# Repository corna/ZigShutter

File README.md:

# ZigShutter

ZigShutter is a platform for the control of window shutters and IAS.

It features:
 * ZigBee connectivity through a nRF52840 module
 * AC power supply
 * Control of two outputs with SSR, to control the two directions of a window shutter motor
 * Two inputs for window opening sensors
 * Eight GPIOs

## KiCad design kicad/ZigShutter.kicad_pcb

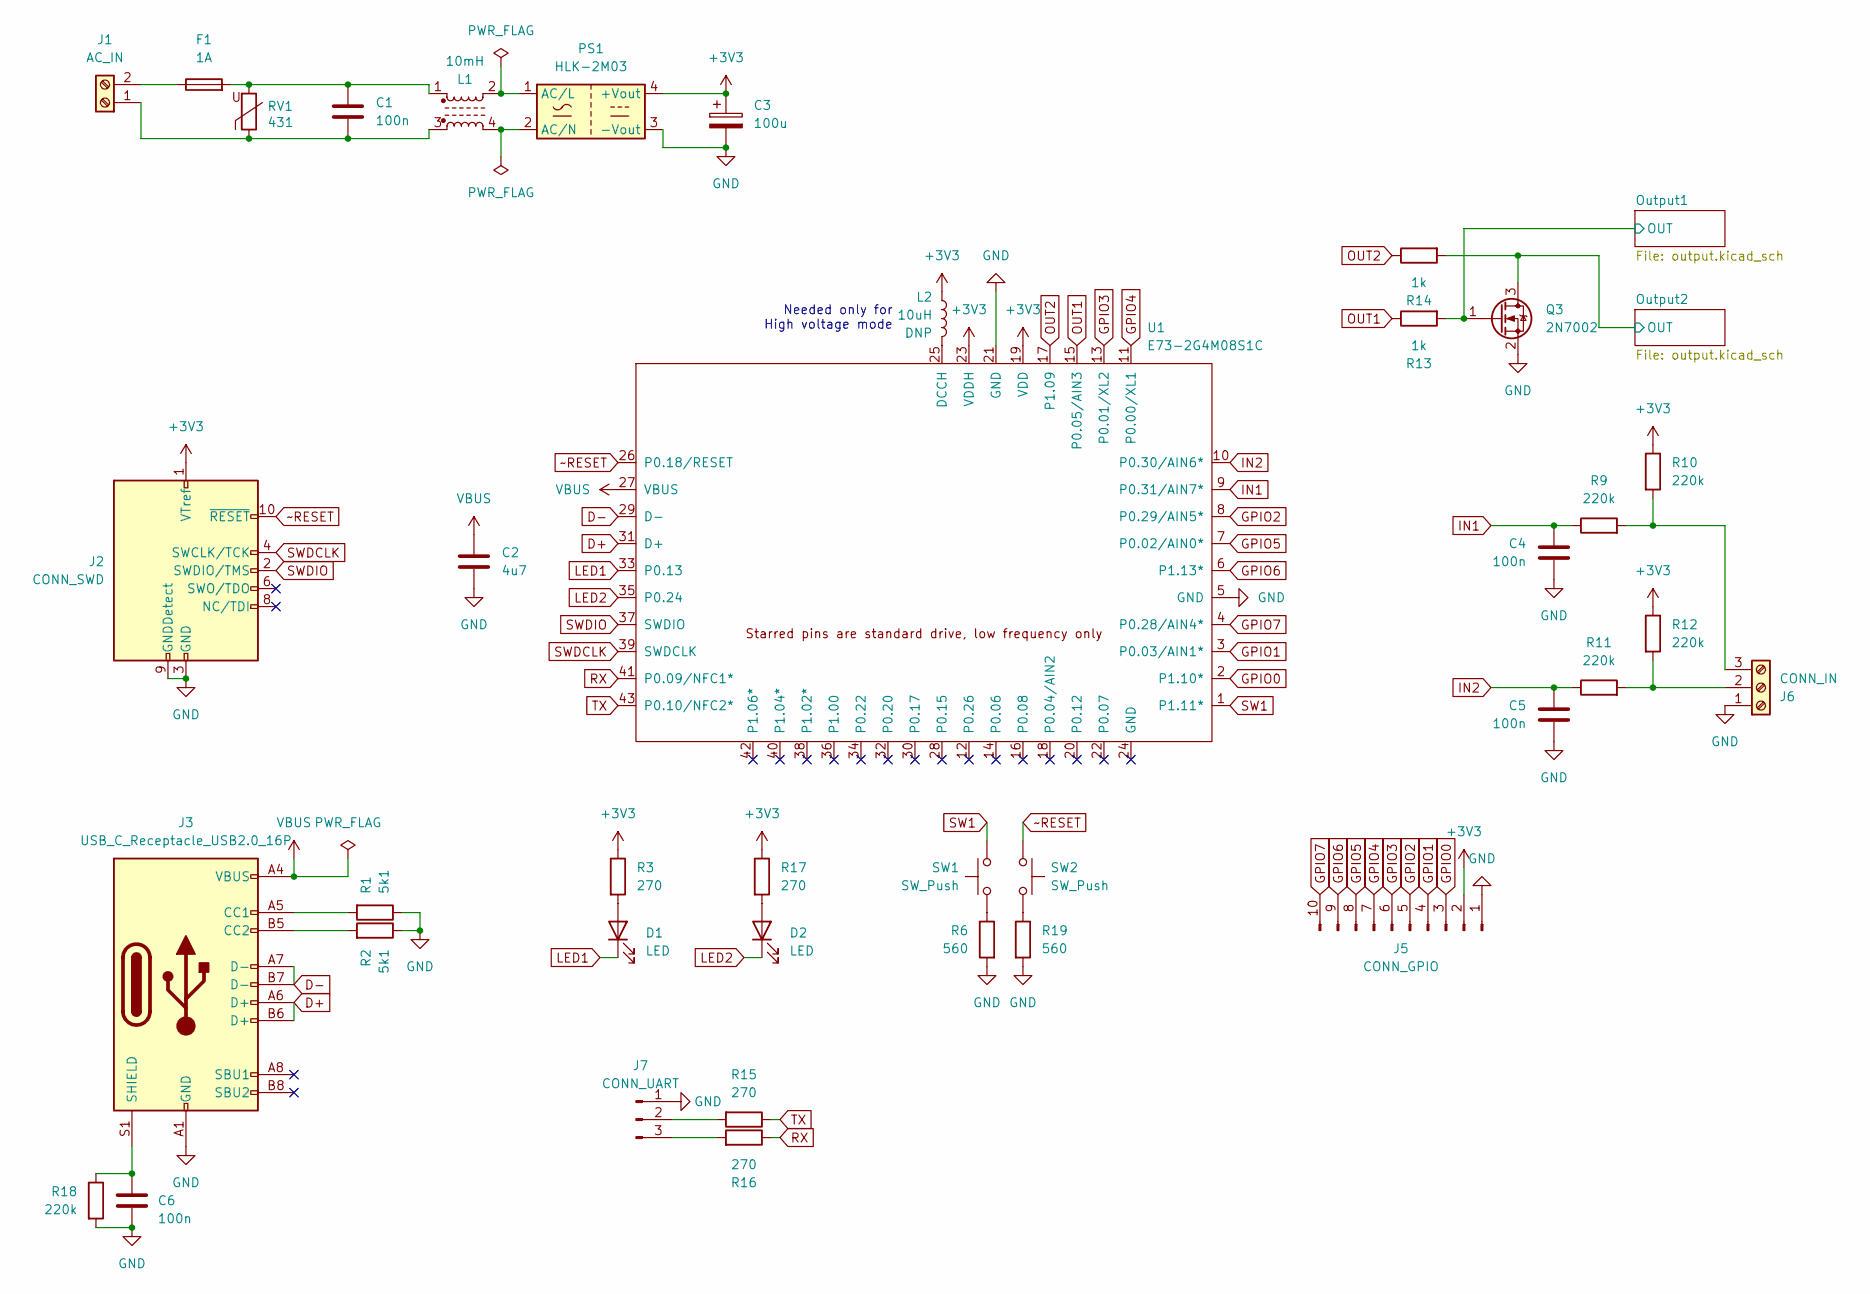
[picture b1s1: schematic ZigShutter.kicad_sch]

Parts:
C1: 100n; C_Rect_L11.5mm_W5.0mm_P10.00mm_MKT
C2: 4u7; C_0603_1608Metric
C3: 100u; CP_EIA-3528-21_Kemet-B
C4, C5, C6: 100n; C_0603_1608Metric
D1, D2: LED; LED_0603_1608Metric
F1: 1A; XFCN_PTF-77
J1: AC_IN; TerminalBlock_Phoenix_MKDS-1,5-2_1x02_P5.00mm_Horizontal
J2: CONN_SWD; PinHeader_2x05_P1.27mm_Vertical_SMD
J3: USB_C_Receptacle_USB2.0_16P; USB_C_Receptacle_XKB_U262_161N_4BSS73_T
J5: CONN_GPIO; PinHeader_1x10_P2.54mm_Vertical
J6: CONN_IN; TerminalBlock_Phoenix_MPT-0,5-3-2.54_1x03_P2.54mm_Horizontal
J7: CONN_UART; PinHeader_1x03_P2.54mm_Vertical
L1: 10mH; UU9.8
L2: 10uH; L_0805_2012Metric
PS1: HLK-2M03; Converter_ACDC_Hi-Link_HLK-2Mxx
Q3: 2N7002; SOT-23
R1, R2: 5k1; R_0603_1608Metric
R3, R15, R16, R17: 270; R_0603_1608Metric
R6, R19: 560; R_0603_1608Metric
R9, R10, R11, R12, R18: 220k; R_0603_1608Metric
R13, R14: 1k; R_0603_1608Metric
RV1: 431; RV_3225
SW1, SW2: SW_Push; SW_Push_SPST_NO_Alps_SKRK
U1: E73-2G4M08S1C

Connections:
+3V3: C3.1, J2.1 (VTref), J5.2, L2.1, PS1.4 (+Vout), R3.1, R10.1, R12.1, R17.1, U1.19 (VDD), U1.23 (VDDH); also elsewhere on the board
/Output1/OUT: Q3.1 (G), R13.2; also elsewhere on the board
/Output2/OUT: Q3.3 (D), R14.2; also elsewhere on the board
D+: J3.A6 (D+), J3.B6 (D+), U1.31 (D+)
D-: J3.A7 (D-), J3.B7 (D-), U1.29 (D-)
GND: C2.2, C3.2, C4.2, C5.2, C6.2, J2.3 (GND), J2.5 (GND), J2.9 (GNDDetect), J3.A1 (GND), J3.A12 (GND), J3.B1 (GND), J3.B12 (GND), J5.1, J6.1, J7.1, PS1.3 (-Vout), Q3.2 (S), R1.1, R2.1, R6.2, R18.2, R19.2, U1.5 (GND), U1.21 (GND); also elsewhere on the board
GPIO0: J5.3, U1.2 (P1.10*)
GPIO1: J5.4, U1.3 (P0.03/AIN1*)
GPIO2: J5.5, U1.8 (P0.29/AIN5*)
GPIO3: J5.6, U1.13 (P0.01/XL2)
GPIO4: J5.7, U1.11 (P0.00/XL1)
GPIO5: J5.8, U1.7 (P0.02/AIN0*)
GPIO6: J5.9, U1.6 (P1.13*)
GPIO7: J5.10, U1.4 (P0.28/AIN4*)
IN1: C4.1, R9.1, U1.9 (P0.31/AIN7*)
IN2: C5.1, R11.1, U1.10 (P0.30/AIN6*)
LED1: D1.1 (K), U1.33 (P0.13)
LED2: D2.1 (K), U1.35 (P0.24)
unnamed: C1.1, F1.2, L1.1, RV1.2
unnamed: D1.2 (A), R3.2
unnamed: D2.2 (A), R17.2
unnamed: C1.2, J1.1, L1.3, RV1.1
unnamed: F1.1, J1.2
unnamed: J3.A5 (CC1), R1.2
unnamed: J3.B5 (CC2), R2.2
unnamed: C6.1, J3.S1 (SHIELD), R18.1
unnamed: J6.2, R11.2, R12.2
unnamed: J6.3, R9.2, R10.2
unnamed: J7.2, R15.2
unnamed: J7.3, R16.2
unnamed: L1.2, PS1.1 (AC/L)
unnamed: L1.4, PS1.2 (AC/N)
unnamed: R6.1, SW1.2
unnamed: R19.1, SW2.2
unnamed: L2.2, U1.25 (DCCH)
OUT1: R13.1, U1.15 (P0.05/AIN3)
OUT2: R14.1, U1.17 (P1.09)
RX: R16.1, U1.41 (P0.09/NFC1*)
SW1: SW1.1, U1.1 (P1.11*)
SWDCLK: J2.4 (SWCLK/TCK), U1.39 (SWDCLK)
SWDIO: J2.2 (SWDIO/TMS), U1.37 (SWDIO)
TX: R15.1, U1.43 (P0.10/NFC2*)
VBUS: C2.1, J3.A4 (VBUS), J3.A9 (VBUS), J3.B4 (VBUS), J3.B9 (VBUS), U1.27 (VBUS)
~RESET: J2.10 (~RESET), SW2.1, U1.26 (P0.18/RESET)

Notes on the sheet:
Needed only for High voltage mode

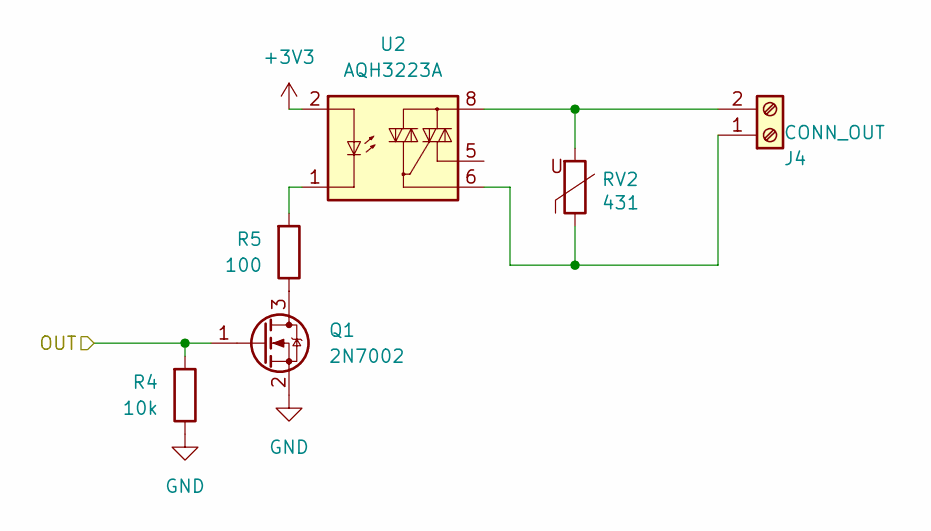
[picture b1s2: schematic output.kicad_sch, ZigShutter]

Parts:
J4: CONN_OUT; TerminalBlock_Phoenix_MKDS-1,5-2_1x02_P5.00mm_Horizontal
Q1: 2N7002; SOT-23
R4: 10k; R_0603_1608Metric
R5: 100; R_0603_1608Metric
RV2: 431; RV_3225
U2: AQH3223A; SSO-7-8_6.4x9.78mm_P2.54mm

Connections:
+3V3: U2.2; also elsewhere on the board
/Output1/OUT: Q1.1 (G), R4.2; also elsewhere on the board
GND: Q1.2 (S), R4.1; also elsewhere on the board
unnamed: J4.1, RV2.1, U2.6
unnamed: J4.2, RV2.2, U2.8
unnamed: Q1.3 (D), R5.1
unnamed: R5.2, U2.1, U2.3, U2.4

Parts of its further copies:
J8: CONN_OUT; TerminalBlock_Phoenix_MKDS-1,5-2_1x02_P5.00mm_Horizontal
Q2: 2N7002; SOT-23
R7: 10k; R_0603_1608Metric
R8: 100; R_0603_1608Metric
RV3: 431; RV_3225
U3: AQH3223A; SSO-7-8_6.4x9.78mm_P2.54mm

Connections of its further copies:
+3V3: U3.2; also elsewhere on the board
/Output2/OUT: Q2.1 (G), R7.2; also elsewhere on the board
GND: Q2.2 (S), R7.1; also elsewhere on the board
unnamed: J8.1, RV3.1, U3.6
unnamed: J8.2, RV3.2, U3.8
unnamed: Q2.3 (D), R8.1
unnamed: R8.2, U3.1, U3.3, U3.4

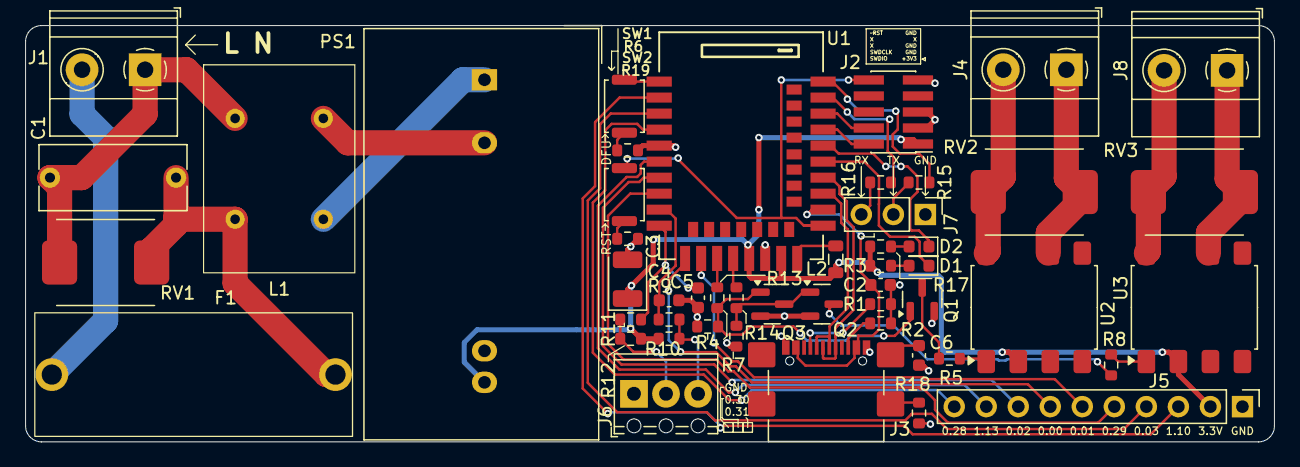
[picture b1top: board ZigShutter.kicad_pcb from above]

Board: 2 copper layers, 99.1 x 33.0 mm, 50 parts (0 on the bottom side), 52 nets.

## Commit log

2024-05-19 Add KiCad files
2024-06-17 Add bootloader files
2024-06-17 Add Zephyr board definition files

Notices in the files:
kicad/ZigShutter.kicad_pcb:
Licensed under CERN-OHL-S v2 or any later version
